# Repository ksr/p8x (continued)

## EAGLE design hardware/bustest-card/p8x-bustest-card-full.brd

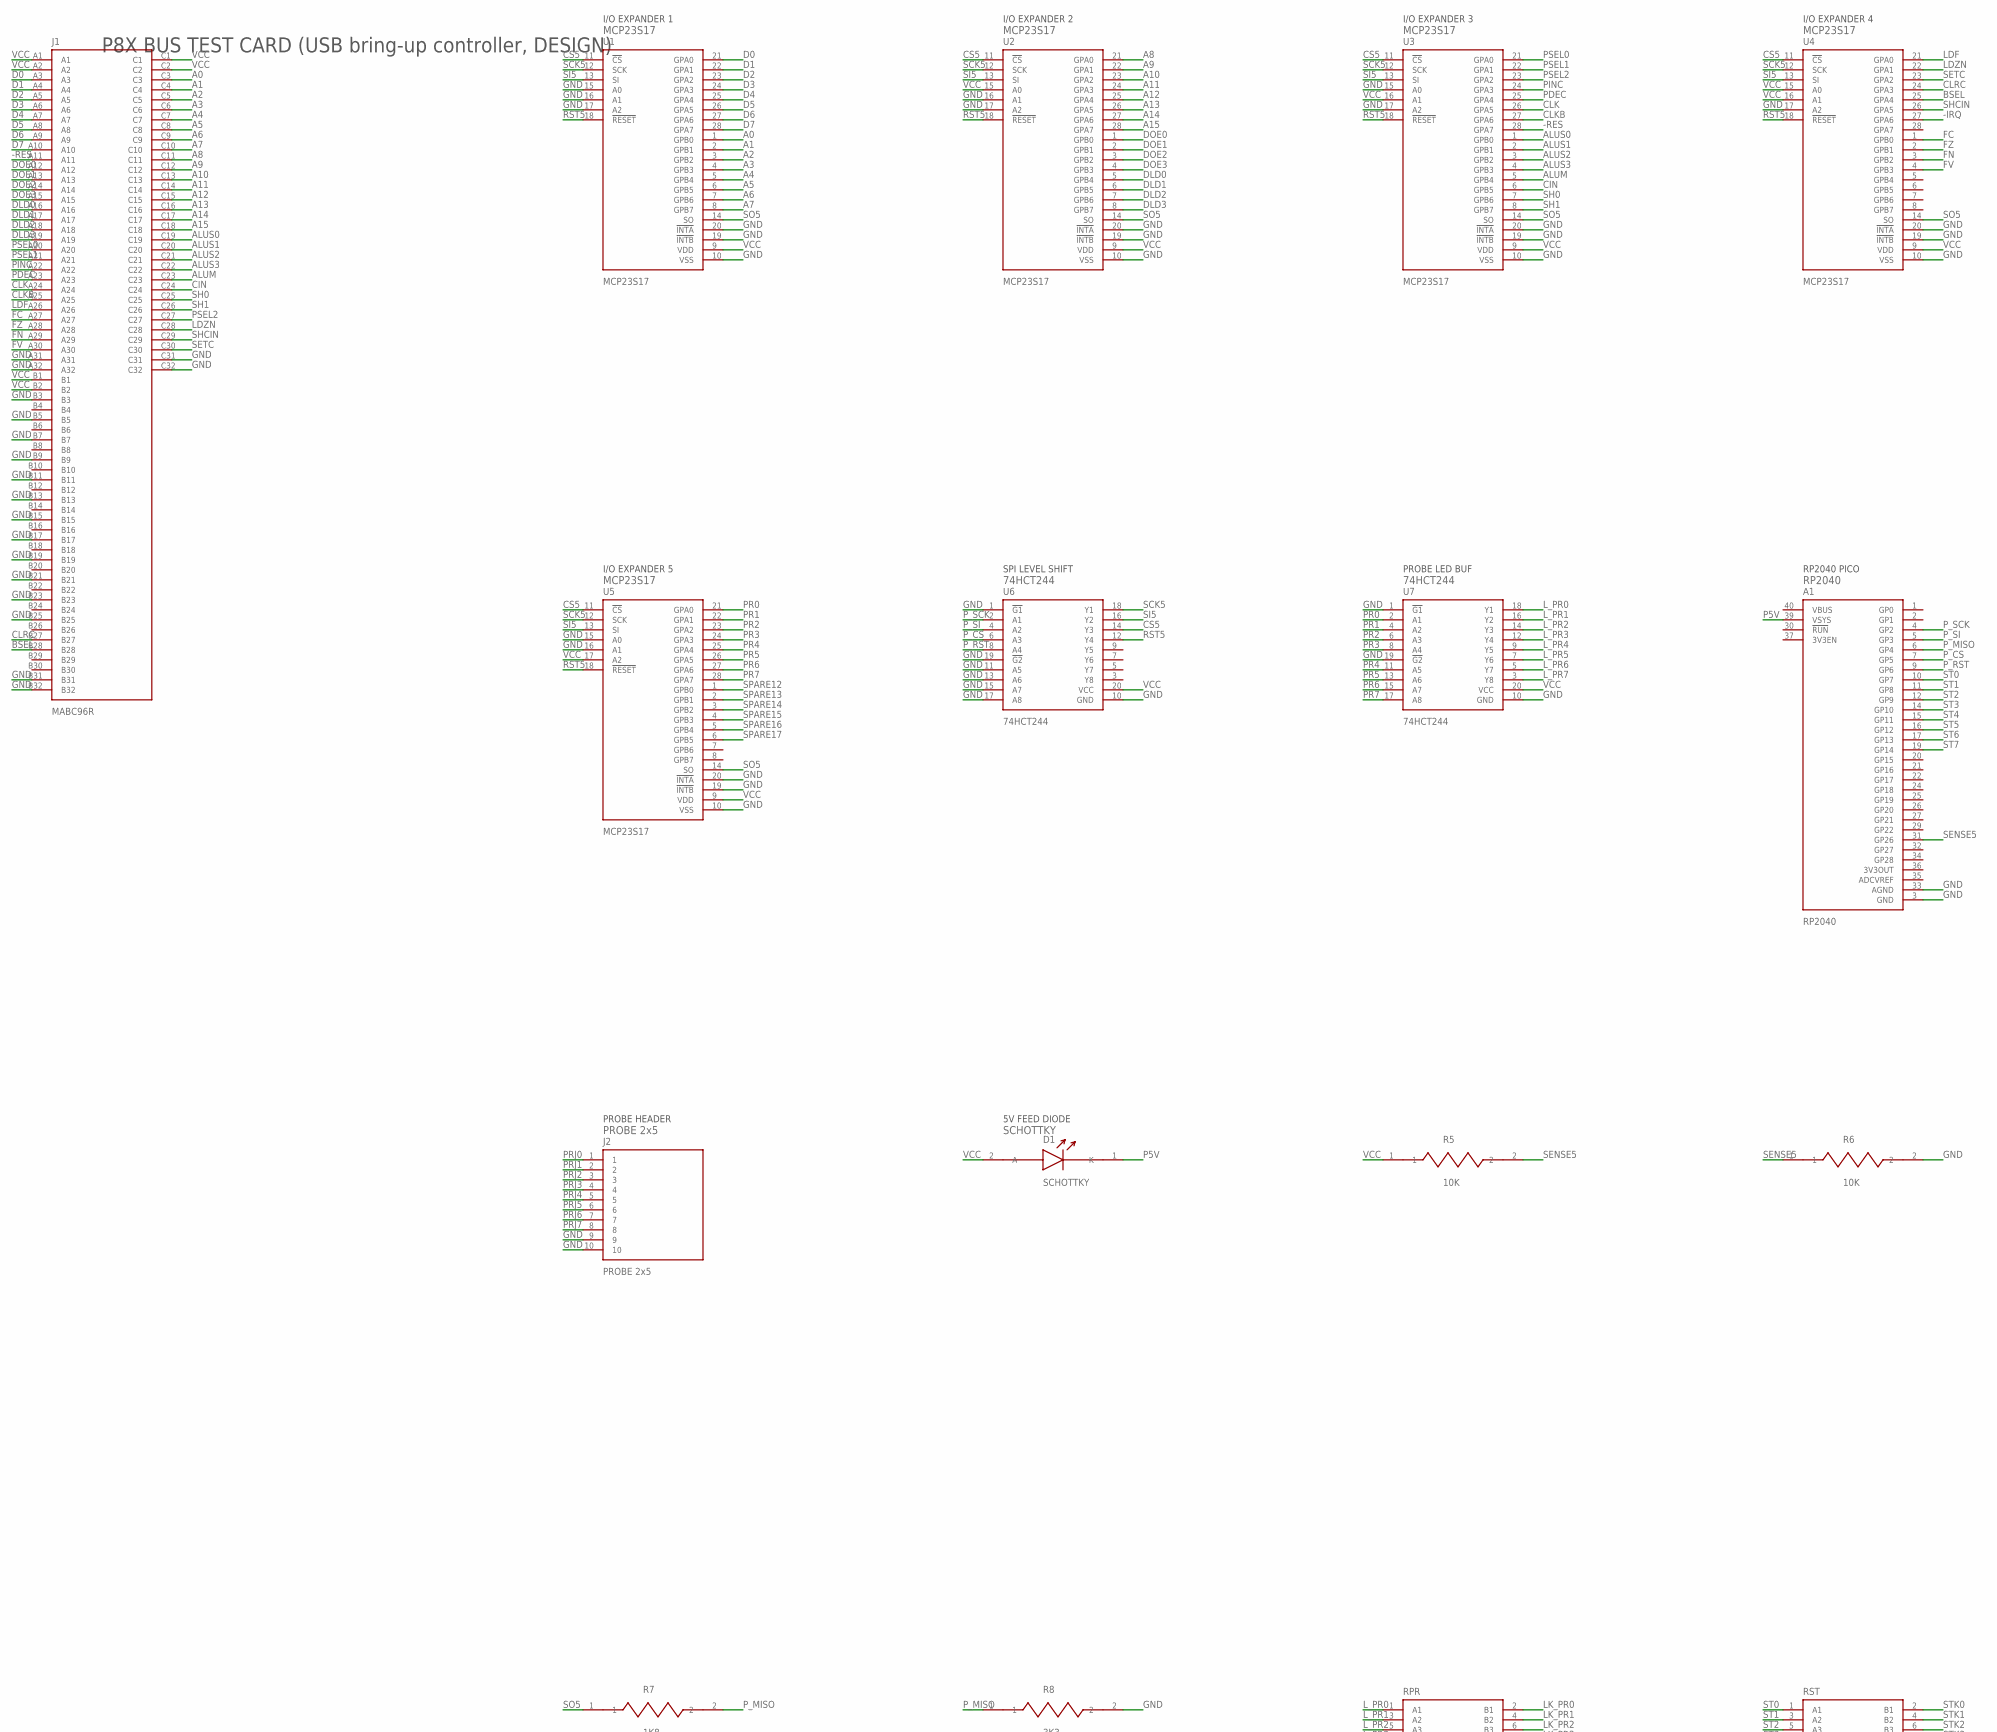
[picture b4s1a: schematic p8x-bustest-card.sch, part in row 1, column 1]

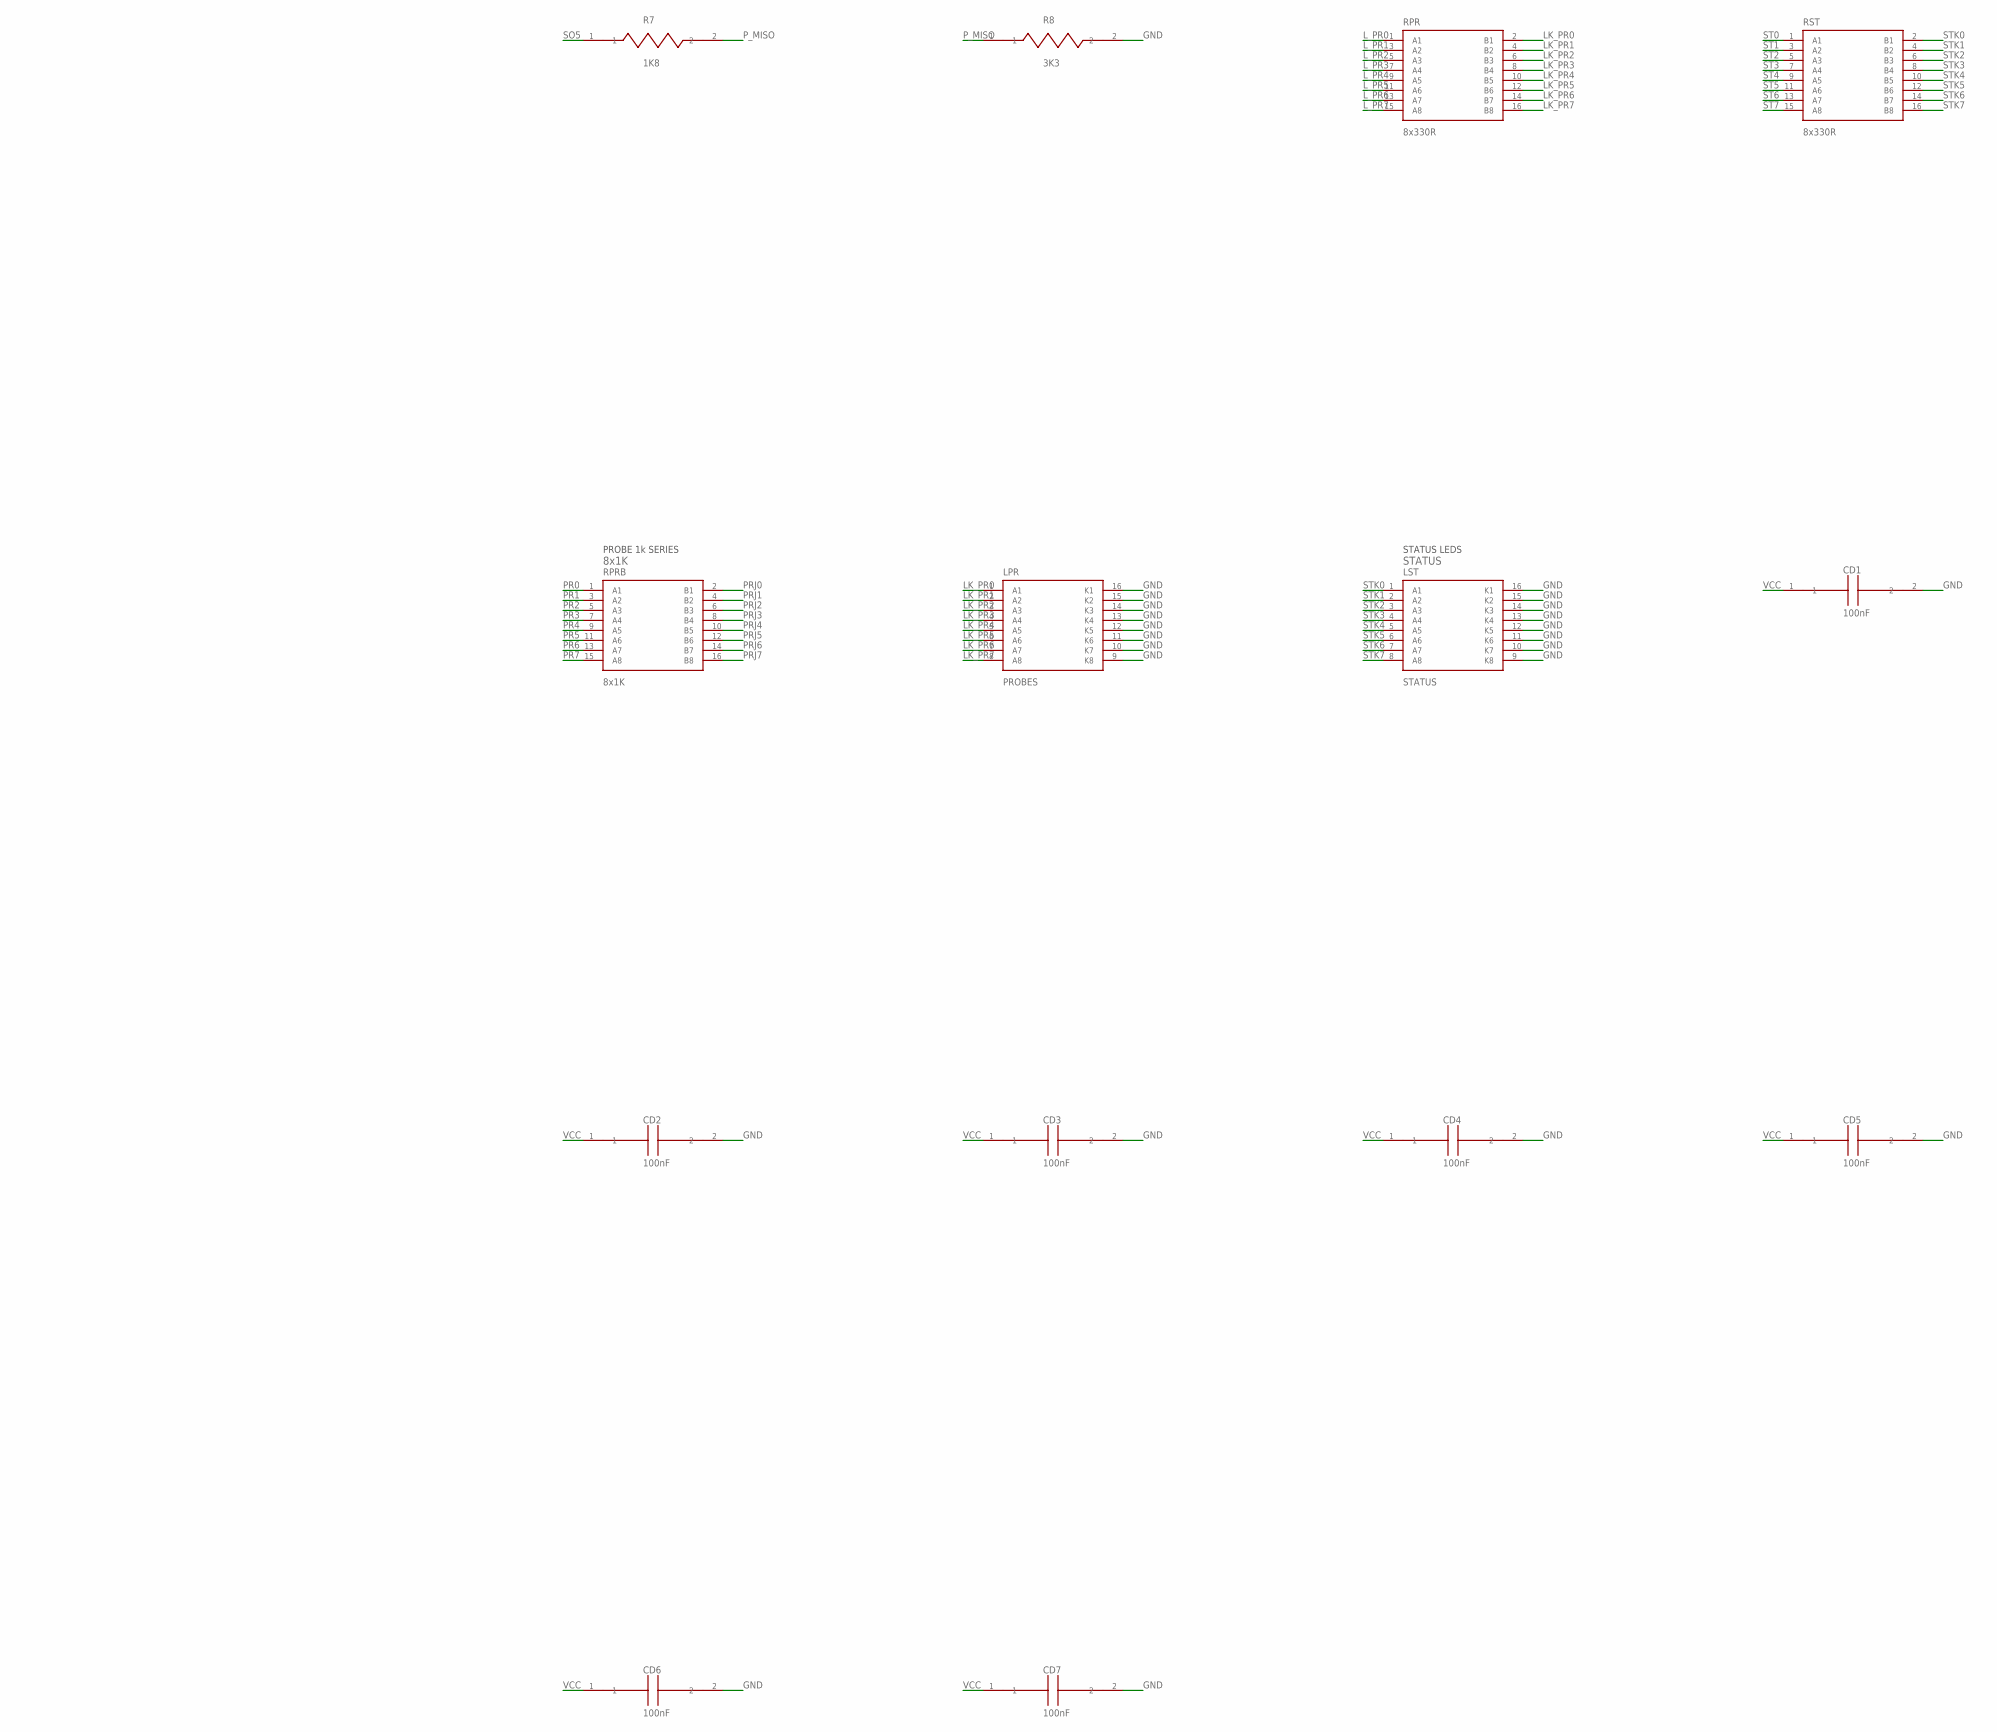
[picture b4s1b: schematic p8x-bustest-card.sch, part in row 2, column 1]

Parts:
A1: RP2040; PICO40
CD1, CD2, CD3, CD4, CD5, CD6, CD7: 100nF; C_DISC1
D1: SCHOTTKY; LED5
J1: MABC96R
J2: PROBE 2x5; HDR10
LPR: PROBES; DIP16
LST: STATUS; DIP16
R5, R6: 10K; R_AXIAL
R7: 1K8; R_AXIAL
R8: 3K3; R_AXIAL
RPR: 8x330R; SIP16
RPRB: 8x1K; SIP16
RST: 8x330R; SIP16
U1, U2, U3, U4, U5: MCP23S17; DIP28N
U6, U7: 74HCT244; DIP20

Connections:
-IRQ: U4.27 (GPA6)
-RES: J1.A11, U3.28 (GPA7)
A0: J1.C3, U1.1 (GPB0)
A1: J1.C4, U1.2 (GPB1)
A2: J1.C5, U1.3 (GPB2)
A3: J1.C6, U1.4 (GPB3)
A4: J1.C7, U1.5 (GPB4)
A5: J1.C8, U1.6 (GPB5)
A6: J1.C9, U1.7 (GPB6)
A7: J1.C10, U1.8 (GPB7)
A8: J1.C11, U2.21 (GPA0)
A9: J1.C12, U2.22 (GPA1)
A10: J1.C13, U2.23 (GPA2)
A11: J1.C14, U2.24 (GPA3)
A12: J1.C15, U2.25 (GPA4)
A13: J1.C16, U2.26 (GPA5)
A14: J1.C17, U2.27 (GPA6)
A15: J1.C18, U2.28 (GPA7)
ALUM: J1.C23, U3.5 (GPB4)
ALUS0: J1.C19, U3.1 (GPB0)
ALUS1: J1.C20, U3.2 (GPB1)
ALUS2: J1.C21, U3.3 (GPB2)
ALUS3: J1.C22, U3.4 (GPB3)
BSEL: J1.B28, U4.25 (GPA4)
CIN: J1.C24, U3.6 (GPB5)
CLK: J1.A24, U3.26 (GPA5)
CLKB: J1.A25, U3.27 (GPA6)
CLRC: J1.B27, U4.24 (GPA3)
CS5: U1.11 (!CS), U2.11 (!CS), U3.11 (!CS), U4.11 (!CS), U5.11 (!CS), U6.14 (Y3)
D0: J1.A3, U1.21 (GPA0)
D1: J1.A4, U1.22 (GPA1)
D2: J1.A5, U1.23 (GPA2)
D3: J1.A6, U1.24 (GPA3)
D4: J1.A7, U1.25 (GPA4)
D5: J1.A8, U1.26 (GPA5)
D6: J1.A9, U1.27 (GPA6)
D7: J1.A10, U1.28 (GPA7)
DLD0: J1.A16, U2.5 (GPB4)
DLD1: J1.A17, U2.6 (GPB5)
DLD2: J1.A18, U2.7 (GPB6)
DLD3: J1.A19, U2.8 (GPB7)
DOE0: J1.A12, U2.1 (GPB0)
DOE1: J1.A13, U2.2 (GPB1)
DOE2: J1.A14, U2.3 (GPB2)
DOE3: J1.A15, U2.4 (GPB3)
FC: J1.A27, U4.1 (GPB0)
FN: J1.A29, U4.3 (GPB2)
FV: J1.A30, U4.4 (GPB3)
FZ: J1.A28, U4.2 (GPB1)
GND: A1.3 (GND), A1.33 (AGND), CD1.2, CD2.2, CD3.2, CD4.2, CD5.2, CD6.2, CD7.2, J1.A31, J1.A32, J1.B3, J1.B5, J1.B7, J1.B9, J1.B11, J1.B13, J1.B15, J1.B17, J1.B19, J1.B21, J1.B23, J1.B25, J1.B31, J1.B32, J1.C31, J1.C32, J2.9, J2.10, LPR.9 (K8), LPR.10 (K7), LPR.11 (K6), LPR.12 (K5), LPR.13 (K4), LPR.14 (K3), LPR.15 (K2), LPR.16 (K1), LST.9 (K8), LST.10 (K7), LST.11 (K6), LST.12 (K5), LST.13 (K4), LST.14 (K3), LST.15 (K2), LST.16 (K1), R6.2, R8.2, U1.10 (VSS), U1.15 (A0), U1.16 (A1), U1.17 (A2), U1.19 (!INTB), U1.20 (!INTA), U2.10 (VSS), U2.16 (A1), U2.17 (A2), U2.19 (!INTB), U2.20 (!INTA), U3.10 (VSS), U3.15 (A0), U3.17 (A2), U3.19 (!INTB), U3.20 (!INTA), U4.10 (VSS), U4.17 (A2), U4.19 (!INTB), U4.20 (!INTA), U5.10 (VSS), U5.15 (A0), U5.16 (A1), U5.19 (!INTB), U5.20 (!INTA), U6.1 (!G1), U6.10 (GND), U6.11 (A5), U6.13 (A6), U6.15 (A7), U6.17 (A8), U6.19 (!G2), U7.1 (!G1), U7.10 (GND), U7.19 (!G2)
LDF: J1.A26, U4.21 (GPA0)
LDZN: J1.C28, U4.22 (GPA1)
LK_PR0: LPR.1 (A1), RPR.2 (B1)
LK_PR1: LPR.2 (A2), RPR.4 (B2)
LK_PR2: LPR.3 (A3), RPR.6 (B3)
LK_PR3: LPR.4 (A4), RPR.8 (B4)
LK_PR4: LPR.5 (A5), RPR.10 (B5)
LK_PR5: LPR.6 (A6), RPR.12 (B6)
LK_PR6: LPR.7 (A7), RPR.14 (B7)
LK_PR7: LPR.8 (A8), RPR.16 (B8)
L_PR0: RPR.1 (A1), U7.18 (Y1)
L_PR1: RPR.3 (A2), U7.16 (Y2)
L_PR2: RPR.5 (A3), U7.14 (Y3)
L_PR3: RPR.7 (A4), U7.12 (Y4)
L_PR4: RPR.9 (A5), U7.9 (Y5)
L_PR5: RPR.11 (A6), U7.7 (Y6)
L_PR6: RPR.13 (A7), U7.5 (Y7)
L_PR7: RPR.15 (A8), U7.3 (Y8)
P5V: A1.39 (VSYS), D1.1 (K)
PDEC: J1.A23, U3.25 (GPA4)
PINC: J1.A22, U3.24 (GPA3)
PR0: RPRB.1 (A1), U5.21 (GPA0), U7.2 (A1)
PR1: RPRB.3 (A2), U5.22 (GPA1), U7.4 (A2)
PR2: RPRB.5 (A3), U5.23 (GPA2), U7.6 (A3)
PR3: RPRB.7 (A4), U5.24 (GPA3), U7.8 (A4)
PR4: RPRB.9 (A5), U5.25 (GPA4), U7.11 (A5)
PR5: RPRB.11 (A6), U5.26 (GPA5), U7.13 (A6)
PR6: RPRB.13 (A7), U5.27 (GPA6), U7.15 (A7)
PR7: RPRB.15 (A8), U5.28 (GPA7), U7.17 (A8)
PRJ0: J2.1, RPRB.2 (B1)
PRJ1: J2.2, RPRB.4 (B2)
PRJ2: J2.3, RPRB.6 (B3)
PRJ3: J2.4, RPRB.8 (B4)
PRJ4: J2.5, RPRB.10 (B5)
PRJ5: J2.6, RPRB.12 (B6)
PRJ6: J2.7, RPRB.14 (B7)
PRJ7: J2.8, RPRB.16 (B8)
PSEL0: J1.A20, U3.21 (GPA0)
PSEL1: J1.A21, U3.22 (GPA1)
PSEL2: J1.C27, U3.23 (GPA2)
P_CS: A1.7 (GP5), U6.6 (A3)
P_MISO: A1.6 (GP4), R7.2, R8.1
P_RST: A1.9 (GP6), U6.8 (A4)
P_SCK: A1.4 (GP2), U6.2 (A1)
P_SI: A1.5 (GP3), U6.4 (A2)
RST5: U1.18 (!RESET), U2.18 (!RESET), U3.18 (!RESET), U4.18 (!RESET), U5.18 (!RESET), U6.12 (Y4)
SCK5: U1.12 (SCK), U2.12 (SCK), U3.12 (SCK), U4.12 (SCK), U5.12 (SCK), U6.18 (Y1)
SENSE5: A1.31 (GP26), R5.2, R6.1
SETC: J1.C30, U4.23 (GPA2)
SH0: J1.C25, U3.7 (GPB6)
SH1: J1.C26, U3.8 (GPB7)
SHCIN: J1.C29, U4.26 (GPA5)
SI5: U1.13 (SI), U2.13 (SI), U3.13 (SI), U4.13 (SI), U5.13 (SI), U6.16 (Y2)
SO5: R7.1, U1.14 (SO), U2.14 (SO), U3.14 (SO), U4.14 (SO), U5.14 (SO)
SPARE12: U5.1 (GPB0)
SPARE13: U5.2 (GPB1)
SPARE14: U5.3 (GPB2)
SPARE15: U5.4 (GPB3)
SPARE16: U5.5 (GPB4)
SPARE17: U5.6 (GPB5)
ST0: A1.10 (GP7), RST.1 (A1)
ST1: A1.11 (GP8), RST.3 (A2)
ST2: A1.12 (GP9), RST.5 (A3)
ST3: A1.14 (GP10), RST.7 (A4)
ST4: A1.15 (GP11), RST.9 (A5)
ST5: A1.16 (GP12), RST.11 (A6)
ST6: A1.17 (GP13), RST.13 (A7)
ST7: A1.19 (GP14), RST.15 (A8)
STK0: LST.1 (A1), RST.2 (B1)
STK1: LST.2 (A2), RST.4 (B2)
STK2: LST.3 (A3), RST.6 (B3)
STK3: LST.4 (A4), RST.8 (B4)
STK4: LST.5 (A5), RST.10 (B5)
STK5: LST.6 (A6), RST.12 (B6)
STK6: LST.7 (A7), RST.14 (B7)
STK7: LST.8 (A8), RST.16 (B8)
VCC: CD1.1, CD2.1, CD3.1, CD4.1, CD5.1, CD6.1, CD7.1, D1.2 (A), J1.A1, J1.A2, J1.B1, J1.B2, J1.C1, J1.C2, R5.1, U1.9 (VDD), U2.9 (VDD), U2.15 (A0), U3.9 (VDD), U3.16 (A1), U4.9 (VDD), U4.15 (A0), U4.16 (A1), U5.9 (VDD), U5.17 (A2), U6.20 (VCC), U7.20 (VCC)

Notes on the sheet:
P8X BUS TEST CARD (USB bring-up controller, DESIGN)
I/O EXPANDER 1
MCP23S17
I/O EXPANDER 2
I/O EXPANDER 3
I/O EXPANDER 4
I/O EXPANDER 5
SPI LEVEL SHIFT
74HCT244
PROBE LED BUF
RP2040 PICO
RP2040
PROBE HEADER
PROBE 2x5
5V FEED DIODE
SCHOTTKY
PROBE 1k SERIES
8x1K
STATUS LEDS
STATUS

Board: 4 copper layers, 27 parts (0 on the bottom side), 120 nets, no tracks yet.

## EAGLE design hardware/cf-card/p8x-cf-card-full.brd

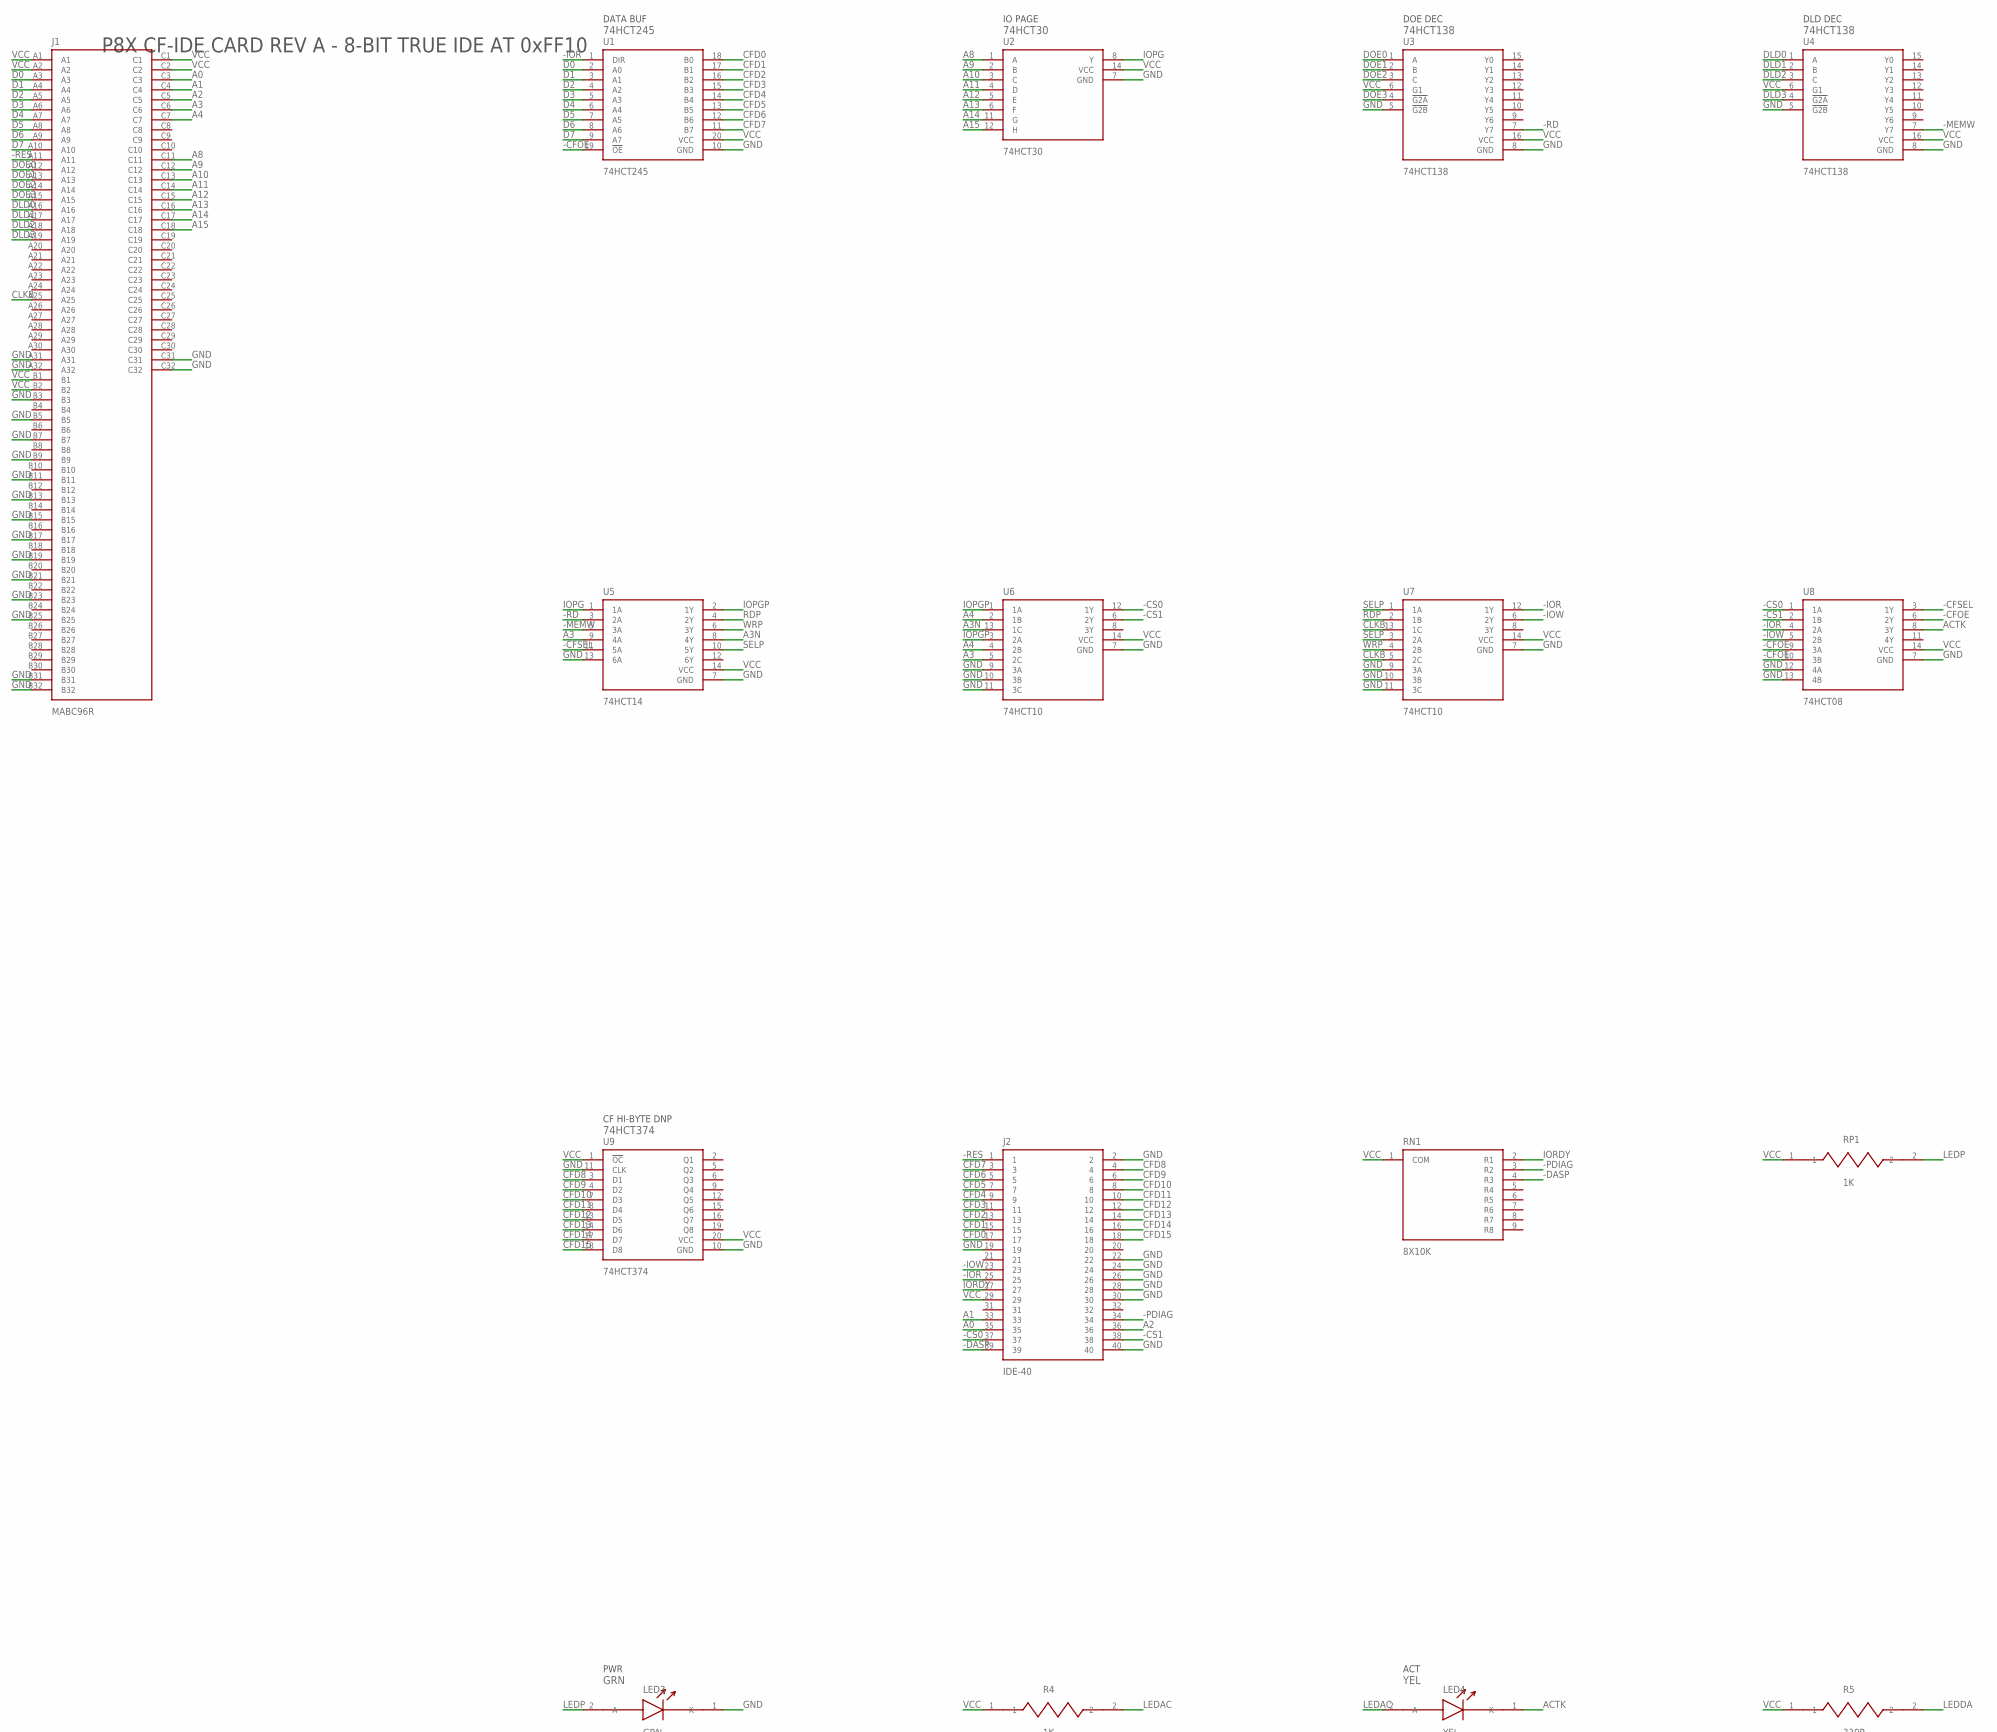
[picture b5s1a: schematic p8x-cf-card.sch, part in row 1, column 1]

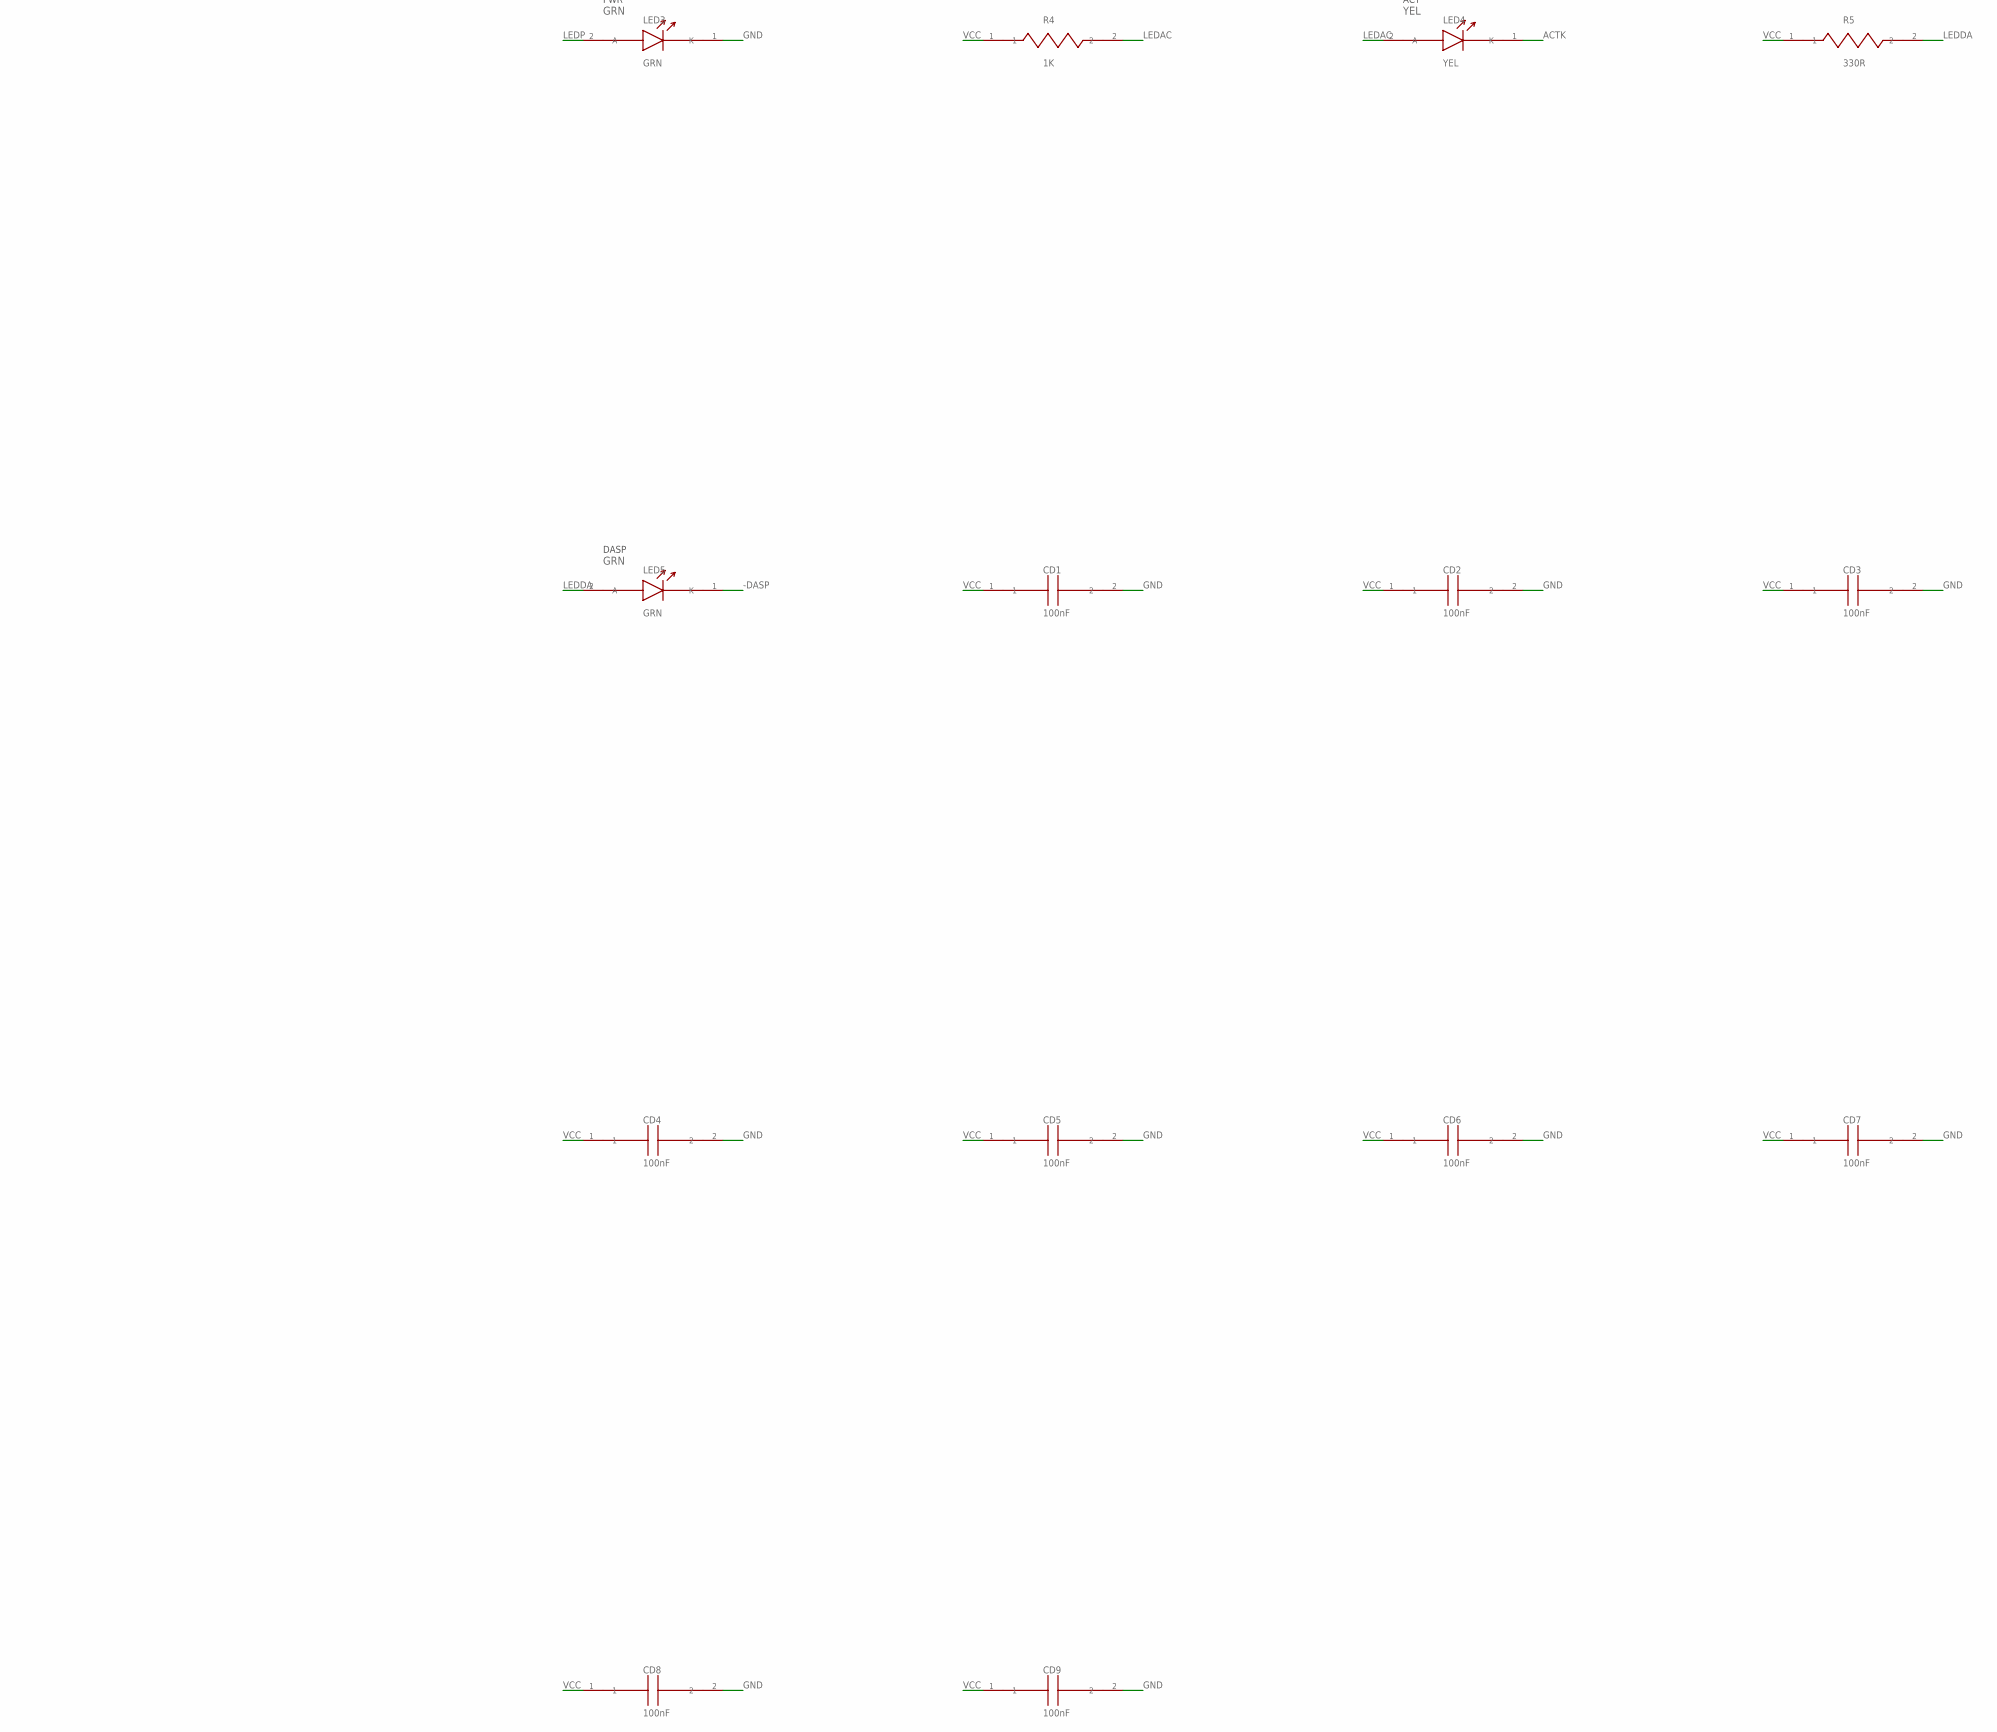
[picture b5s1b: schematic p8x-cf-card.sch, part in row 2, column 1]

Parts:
CD1, CD2, CD3, CD4, CD5, CD6, CD7, CD8, CD9: 100nF; C_DISC1
J1: MABC96R
J2: IDE-40; HDR40
LED3, LED5: GRN; LED5
LED4: YEL; LED5
R4: 1K; R_AXIAL
R5: 330R; R_AXIAL
RN1: 8X10K; SIP9
RP1: 1K; R_AXIAL
U1: 74HCT245; DIP20
U2: 74HCT30; DIP14
U3, U4: 74HCT138; DIP16
U5: 74HCT14; DIP14
U6, U7: 74HCT10; DIP14
U8: 74HCT08; DIP14
U9: 74HCT374; DIP20

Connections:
-CFOE: U1.19 (!OE), U8.6 (2Y), U8.9 (3A), U8.10 (3B)
-CFSEL: U5.11 (5A), U8.3 (1Y)
-CS0: J2.37, U6.12 (1Y), U8.1 (1A)
-CS1: J2.38, U6.6 (2Y), U8.2 (1B)
-DASP: J2.39, LED5.1 (K), RN1.4 (R3)
-IOR: J2.25, U1.1 (DIR), U7.12 (1Y), U8.4 (2A)
-IOW: J2.23, U7.6 (2Y), U8.5 (2B)
-MEMW: U4.7 (Y7), U5.5 (3A)
-PDIAG: J2.34, RN1.3 (R2)
-RD: U3.7 (Y7), U5.3 (2A)
-RES: J1.A11, J2.1
A0: J1.C3, J2.35
A1: J1.C4, J2.33
A2: J1.C5, J2.36
A3: J1.C6, U5.9 (4A), U6.5 (2C)
A3N: U5.8 (4Y), U6.13 (1C)
A4: J1.C7, U6.2 (1B), U6.4 (2B)
A8: J1.C11, U2.1 (A)
A9: J1.C12, U2.2 (B)
A10: J1.C13, U2.3 (C)
A11: J1.C14, U2.4 (D)
A12: J1.C15, U2.5 (E)
A13: J1.C16, U2.6 (F)
A14: J1.C17, U2.11 (G)
A15: J1.C18, U2.12 (H)
ACTK: LED4.1 (K), U8.8 (3Y)
CFD0: J2.17, U1.18 (B0)
CFD1: J2.15, U1.17 (B1)
CFD2: J2.13, U1.16 (B2)
CFD3: J2.11, U1.15 (B3)
CFD4: J2.9, U1.14 (B4)
CFD5: J2.7, U1.13 (B5)
CFD6: J2.5, U1.12 (B6)
CFD7: J2.3, U1.11 (B7)
CFD8: J2.4, U9.3 (D1)
CFD9: J2.6, U9.4 (D2)
CFD10: J2.8, U9.7 (D3)
CFD11: J2.10, U9.8 (D4)
CFD12: J2.12, U9.13 (D5)
CFD13: J2.14, U9.14 (D6)
CFD14: J2.16, U9.17 (D7)
CFD15: J2.18, U9.18 (D8)
CLKB: J1.A25, U7.5 (2C), U7.13 (1C)
D0: J1.A3, U1.2 (A0)
D1: J1.A4, U1.3 (A1)
D2: J1.A5, U1.4 (A2)
D3: J1.A6, U1.5 (A3)
D4: J1.A7, U1.6 (A4)
D5: J1.A8, U1.7 (A5)
D6: J1.A9, U1.8 (A6)
D7: J1.A10, U1.9 (A7)
DLD0: J1.A16, U4.1 (A)
DLD1: J1.A17, U4.2 (B)
DLD2: J1.A18, U4.3 (C)
DLD3: J1.A19, U4.4 (!G2A)
DOE0: J1.A12, U3.1 (A)
DOE1: J1.A13, U3.2 (B)
DOE2: J1.A14, U3.3 (C)
DOE3: J1.A15, U3.4 (!G2A)
GND: CD1.2, CD2.2, CD3.2, CD4.2, CD5.2, CD6.2, CD7.2, CD8.2, CD9.2, J1.A31, J1.A32, J1.B3, J1.B5, J1.B7, J1.B9, J1.B11, J1.B13, J1.B15, J1.B17, J1.B19, J1.B21, J1.B23, J1.B25, J1.B31, J1.B32, J1.C31, J1.C32, J2.2, J2.19, J2.22, J2.24, J2.26, J2.28, J2.30, J2.40, LED3.1 (K), U1.10 (GND), U2.7 (GND), U3.5 (!G2B), U3.8 (GND), U4.5 (!G2B), U4.8 (GND), U5.7 (GND), U5.13 (6A), U6.7 (GND), U6.9 (3A), U6.10 (3B), U6.11 (3C), U7.7 (GND), U7.9 (3A), U7.10 (3B), U7.11 (3C), U8.7 (GND), U8.12 (4A), U8.13 (4B), U9.10 (GND), U9.11 (CLK)
IOPG: U2.8 (Y), U5.1 (1A)
IOPGP: U5.2 (1Y), U6.1 (1A), U6.3 (2A)
IORDY: J2.27, RN1.2 (R1)
LEDAC: LED4.2 (A), R4.2
LEDDA: LED5.2 (A), R5.2
LEDP: LED3.2 (A), RP1.2
RDP: U5.4 (2Y), U7.2 (1B)
SELP: U5.10 (5Y), U7.1 (1A), U7.3 (2A)
VCC: CD1.1, CD2.1, CD3.1, CD4.1, CD5.1, CD6.1, CD7.1, CD8.1, CD9.1, J1.A1, J1.A2, J1.B1, J1.B2, J1.C1, J1.C2, J2.29, R4.1, R5.1, RN1.1 (COM), RP1.1, U1.20 (VCC), U2.14 (VCC), U3.6 (G1), U3.16 (VCC), U4.6 (G1), U4.16 (VCC), U5.14 (VCC), U6.14 (VCC), U7.14 (VCC), U8.14 (VCC), U9.1 (!OC), U9.20 (VCC)
WRP: U5.6 (3Y), U7.4 (2B)

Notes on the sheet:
P8X CF-IDE CARD REV A - 8-BIT TRUE IDE AT 0xFF10
DATA BUF
74HCT245
IO PAGE
74HCT30
DOE DEC
74HCT138
DLD DEC
CF HI-BYTE DNP
74HCT374
PWR
GRN
ACT
YEL
DASP

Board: 4 copper layers, 27 parts (0 on the bottom side), 70 nets, no tracks yet.
